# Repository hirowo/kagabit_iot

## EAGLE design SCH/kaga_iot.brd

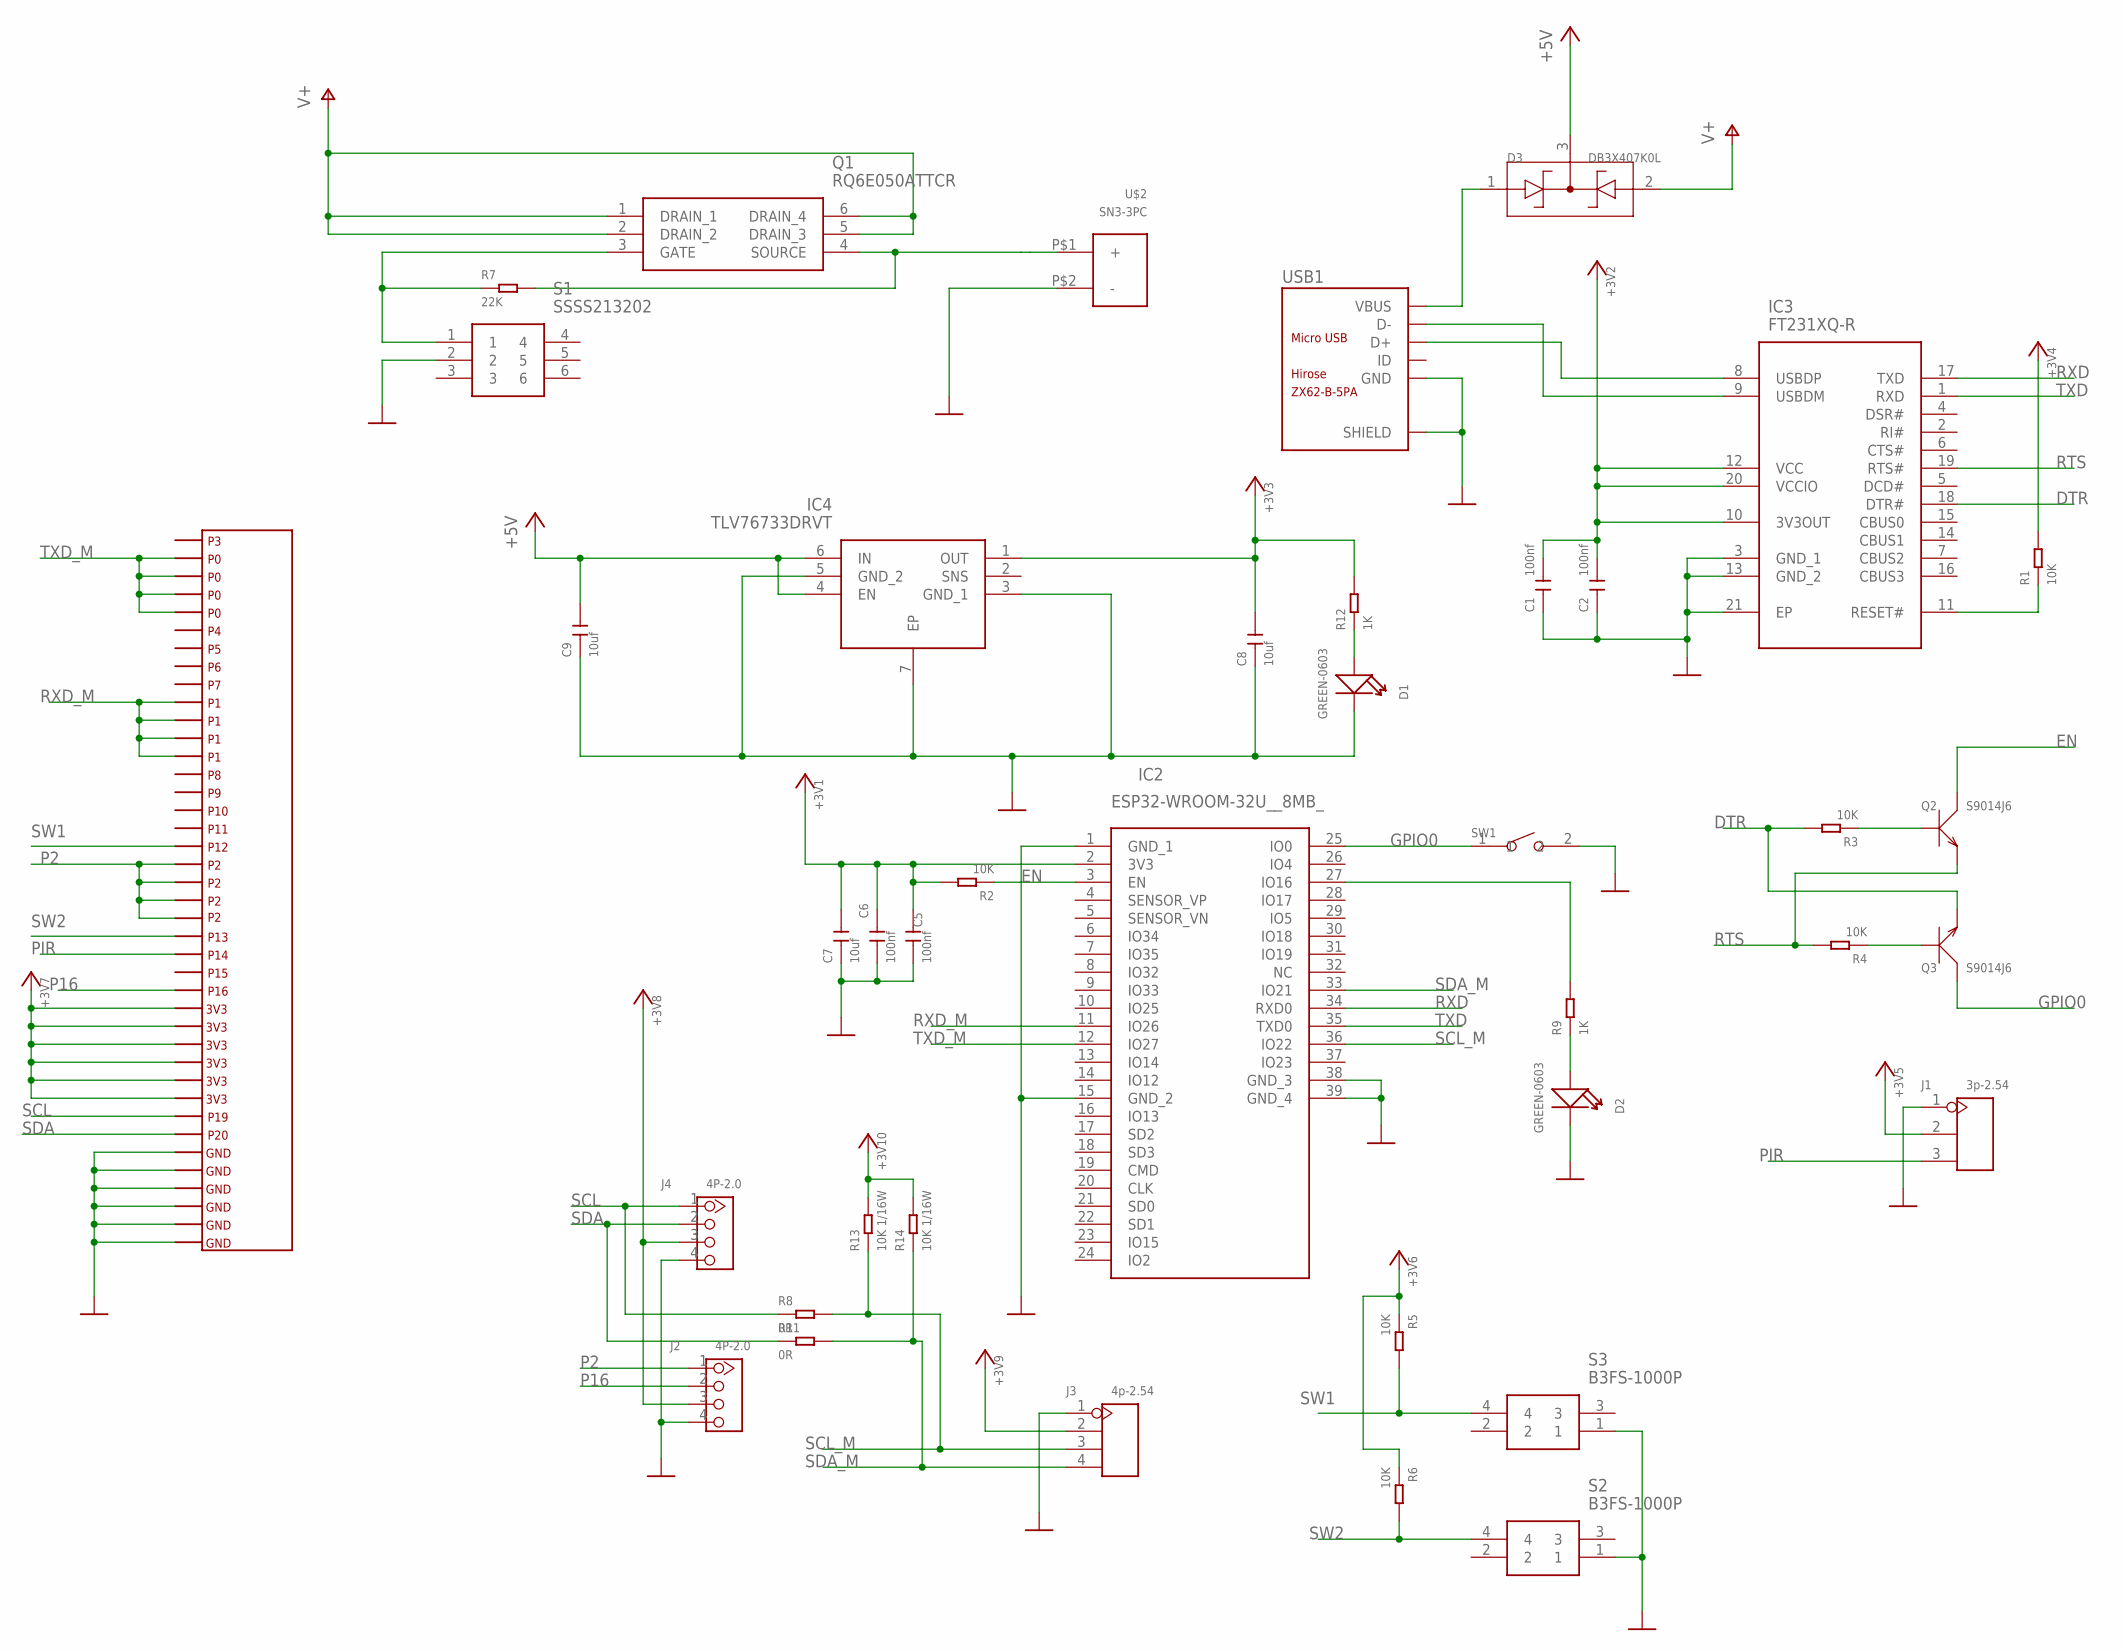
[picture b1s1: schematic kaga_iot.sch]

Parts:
C1, C2, C5, C6: 100nf; C0603
C7, C8, C9: 10uf; C0603
D1, D2: GREEN-0603; LED-0603
D3: DB3X407K0L; SOT-23
IC2: ESP32-WROOM-32U__8MB_; ESP32WROOM32U8MB
IC3: FT231XQ-R; QFN50P400X400X80-21N
IC4: TLV76733DRVT; SON65P200X200X80-7N
J1: 3p-2.54; H3-2.54
J2, J4: 4P-2.0; HW4-2.0
J3: 4p-2.54; H4-2.54
Q1: RQ6E050ATTCR; SOT95P280X100-6N
Q2, Q3: S9014J6; SOT-23
R1, R2, R3, R4, R5, R6: 10K; R0603
R7: 22K; R0402
R8, R11: 0R; R0402
R9, R12: 1K; R0603
R13, R14: 10K 1/16W; R0402
S1: SSSS213202
S2, S3: B3FS-1000P
SW1: SMD-BUTTON(2P-3.0X2.5X1.2+0.4MM)-B3U-1000P-2P-SMD; SW2-2.6-3.0X2.5X1.2+0.4MM
U$1: SMD_BBC_EDG2
U$2: SN3-3PC
USB1: ZX62-B-5PA; MICRO-USB5+6P-SMD-0.65-AB

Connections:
+3V3: C1.2, C2.2, C5.2, C6.2, C7.2, C8.2, IC2.2 (3V3), IC3.10 (3V3OUT), IC3.12 (VCC), IC3.20 (VCCIO), IC4.1 (OUT), J1.2, J2.3, J3.2, J4.3, R1.2, R2.2, R5.1, R6.1, R12.2, R13.2, R14.2, U$1.P$49, U$1.P$50, U$1.P$51, U$1.P$52, U$1.P$53, U$1.P$54
+5V: C9.2, D3.3, IC4.4 (EN), IC4.6 (IN)
DTR: IC3.18 (DTR#), Q3.2 (E), R3.2
EN: IC2.3 (EN), Q2.3 (C), R2.1
GND: C1.1, C2.1, C5.1, C6.1, C7.1, C8.1, C9.1, D1.-, D2.-, IC2.1 (GND_1), IC2.15 (GND_2), IC2.38 (GND_3), IC2.39 (GND_4), IC3.3 (GND_1), IC3.13 (GND_2), IC3.21 (EP), IC4.3 (GND_1), IC4.5 (GND_2), IC4.7 (EP), J1.1, J2.4, J3.1, J4.4, S1.2, S2.1, S3.1, SW1.2, U$1.P$41, U$1.P$42, U$1.P$43, U$1.P$44, U$1.P$45, U$1.P$46, U$2.P$2 (-), USB1.5 (GND), USB1.P1 (SHIELD), USB1.P2 (SHIELD), USB1.P3 (SHIELD), USB1.P4 (SHIELD), USB1.P5 (SHIELD), USB1.P6 (SHIELD)
GPIO0: IC2.25 (IO0), Q3.3 (C), SW1.1
unnamed: IC3.8 (USBDP), USB1.3 (D+)
unnamed: IC3.9 (USBDM), USB1.2 (D-)
unnamed: IC3.11 (RESET#), R1.1
unnamed: D1.+, R12.1
unnamed: D2.+, R9.1
unnamed: IC2.27 (IO16), R9.2
unnamed: Q2.1 (B), R3.1
unnamed: Q3.1 (B), R4.1
unnamed: Q1.4 (SOURCE), R7.2, U$2.P$1 (+)
unnamed: Q1.3 (GATE), R7.1, S1.1
P2: J2.1, U$1.P$59, U$1.P$60, U$1.P$61, U$1.P$62
P16: J2.2, U$1.P$55
PIR: J1.3, U$1.P$57
RTS: IC3.19 (RTS#), Q2.2 (E), R4.2
RXD: IC2.34 (RXD0), IC3.17 (TXD)
RXD_M: IC2.11 (IO26), U$1.P$68, U$1.P$69, U$1.P$70, U$1.P$71
SCL: J4.1, R8.1, U$1.P$48
SCL_M: IC2.36 (IO22), J3.3, R8.2, R13.1
SDA: J4.2, R11.1, U$1.P$47
SDA_M: IC2.33 (IO21), J3.4, R11.2, R14.1
SW1: R5.2, S3.4, U$1.P$63
SW2: R6.2, S2.4, U$1.P$58
TXD: IC2.35 (TXD0), IC3.1 (RXD)
TXD_M: IC2.12 (IO27), U$1.P$76, U$1.P$77, U$1.P$78, U$1.P$79
V+: D3.2, Q1.1 (DRAIN_1), Q1.2 (DRAIN_2), Q1.5 (DRAIN_3), Q1.6 (DRAIN_4)
VBUS: D3.1, USB1.1 (VBUS)

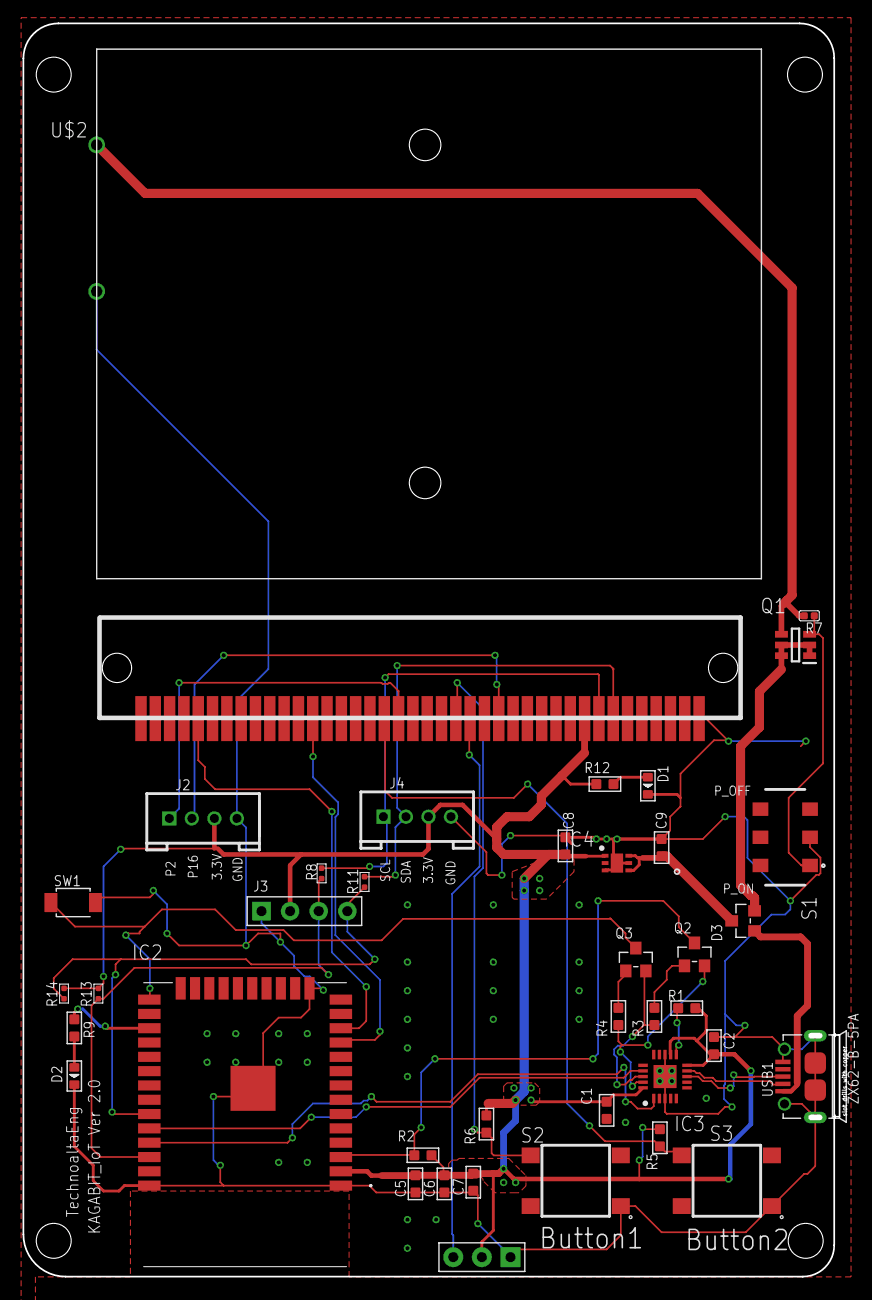
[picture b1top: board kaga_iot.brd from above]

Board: 2 copper layers, 72.9 x 110.9 mm, 40 parts (0 on the bottom side), 32 nets.

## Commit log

2020-09-07 Create WiFiClientBasic_KagaBitIot.ino
    ネットに接続できた最初のバージョン
2020-09-15 Update WiFiClientBasic_KagaBitIot.ino
    WEBサーバーの機能を実装
2020-09-21 Update WiFiClientBasic_KagaBitIot.ino
    AMBIENTにデータを送信する機能をついか
2021-05-20 Update WiFiClientBasic_KagaBitIot.ino
    MQTTに対応
2021-09-02 Update WiFiClientBasic_KagaBitIot.ino
    リリースバージョン1.0
2022-06-20 バージョン２回路図
2022-06-23 ドローン用ファーム追加
2022-10-18 バージョン１．３
